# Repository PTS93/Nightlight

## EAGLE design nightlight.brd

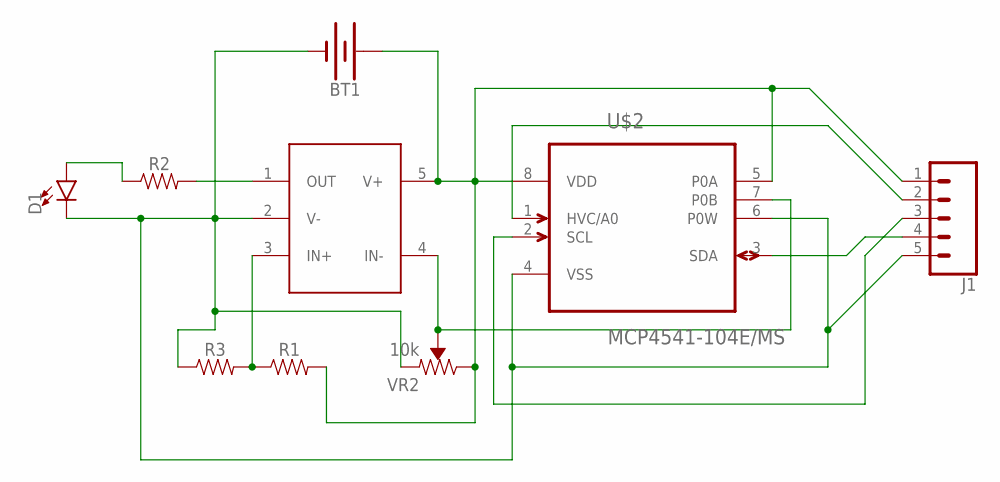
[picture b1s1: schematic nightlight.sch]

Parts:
BT1: BATTERY-20MM_PTH; BATTCOM_20MM_PTH
D1: LED3MM; LED_3MM
J1: CONN_05PTH_LONGPADS; 1X05_LONGPADS
R1, R2, R3: AXIAL-0.3
U$1: TLV8801DBVT; SOT95P280X145-5N
U$2: MCP4541-104E/MS; SOP65P490X110-8N
VR2: 10k; TRIMPOT-PTH-3386U

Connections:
GND: BT1.2 (-), D1.K (C), J1.5, R3.P$1 (1), U$1.2 (V-), U$2.4 (VSS), U$2.6 (P0W), VR2.1 (CCW)
unnamed: R1.P$1 (1), R3.P$2 (2), U$1.3 (IN+)
unnamed: D1.A, R2.P$1 (1)
unnamed: J1.4, U$2.3 (SDA)
unnamed: U$1.4 (IN-), U$2.7 (P0B), VR2.2 (WIPER)
unnamed: J1.3, U$2.2 (SCL)
unnamed: R2.P$2 (2), U$1.1 (OUT)
unnamed: J1.2, U$2.1 (HVC/A0)
VCC: BT1.1 (+), J1.1, R1.P$2 (2), U$1.5 (V+), U$2.5 (P0A), U$2.8 (VDD), VR2.3 (CW)

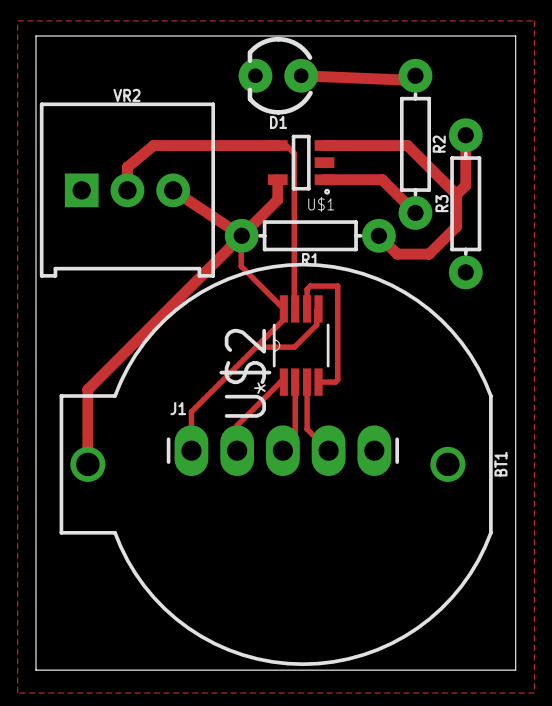
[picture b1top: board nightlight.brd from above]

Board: 2 copper layers, 26.6 x 35.2 mm, 9 parts (0 on the bottom side), 9 nets.

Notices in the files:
parts and their libraries:
SparkFun-Batteries: Licensing: Creative Commons ShareAlike 4.0 International - https://creativecommons.org/licenses/by-sa/4.0
